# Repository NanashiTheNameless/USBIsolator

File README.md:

# USBIsolator

Simple USB isolator board project with two hardware variants:

- `USBIsolator.alt` is the smaller, simpler version and is the version currently used in production.
- `USBIsolator` is the full version and includes the switch-function cheatsheet in its README.

## Project folders:

- [USBIsolator](USBIsolator/) - full version (with cheatsheet)
- [USBIsolator.alt](USBIsolator.alt/) - compact production version

## Production files:

- [USBIsolator production](USBIsolator/production/)
- [USBIsolator.alt production](USBIsolator.alt/production/)

## Cheatsheet

- [USBIsolator.odt](USBIsolator.odt)

```text
SW1:
1 -> USB1: VCC =  USB2: VCC (DEFAULT: ON)
2 -> USB1: D-  =  USB2: D-  (DEFAULT: ON)
3 -> USB1: D+  =  USB2: D+  (DEFAULT: ON)
4 -> USB1: GND =  USB2: GND (DEFAULT: ON)
5 -> USB1: SH  =  USB2: SH  (DEFAULT: ON)

SW2:
1 -> USB2: SH  =  USB2: GND (DEFAULT: OFF)
2 -> USB1: SH  =  USB1: GND (DEFAULT: OFF)
```

## Images

### USBIsolator (full version)

### USBIsolator.alt (production version)

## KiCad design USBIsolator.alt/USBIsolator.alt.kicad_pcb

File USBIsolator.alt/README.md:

# USBIsolator

Simple USB isolator board project (compact production version).

This is the smaller and simpler variant currently used in production.

- For the full version, see [USBIsolator](../USBIsolator/).
- The same switch-function cheatsheet is included below.

## Project folders:

- [USBIsolator](../USBIsolator/) - full version (with cheatsheet)
- [USBIsolator.alt](./) - compact production version

## Production files:

- [USBIsolator production](../USBIsolator/production/)
- [USBIsolator.alt production](production/)

## Cheatsheet

- [USBIsolator.odt](../USBIsolator.odt)

```text
SW1:
1 -> USB1: VCC =  USB2: VCC (DEFAULT: ON)
2 -> USB1: D-  =  USB2: D-  (DEFAULT: ON)
3 -> USB1: D+  =  USB2: D+  (DEFAULT: ON)
4 -> USB1: GND =  USB2: GND (DEFAULT: ON)
5 -> USB1: SH  =  USB2: SH  (DEFAULT: ON)

SW2:
1 -> USB2: SH  =  USB2: GND (DEFAULT: OFF)
2 -> USB1: SH  =  USB1: GND (DEFAULT: OFF)
```

## Images

### USBIsolator.alt (production version)

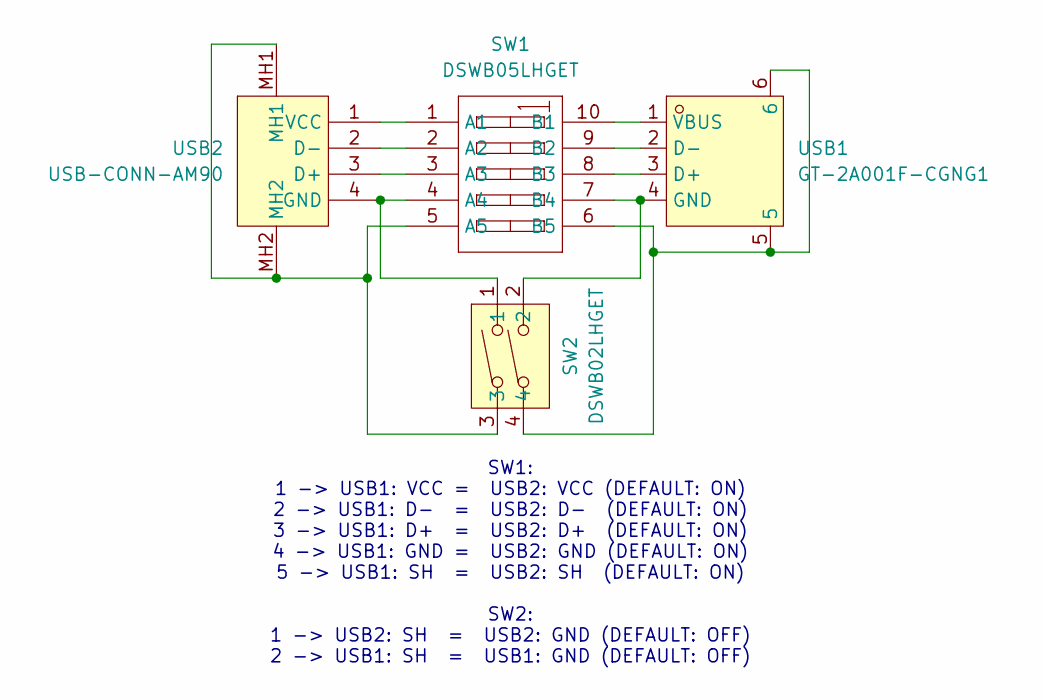
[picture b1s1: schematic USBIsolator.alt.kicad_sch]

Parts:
SW1: DSWB05LHGET; SW-TH_DSWB05LHGET; LCSC Part C126889
SW2: DSWB02LHGET; SW-TH_DSWB02LHGET; LCSC Part C99421
USB1: GT-2A001F-CGNG1; USB-A-TH_AF-90-ZJWG-ZB; LCSC Part C5362632
USB2: USB-CONN-AM90; USB-A-TH_AM90; LCSC Part C9739

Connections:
unnamed: SW1.1 (A1), USB2.1 (VCC)
unnamed: SW1.2 (A2), USB2.2 (D-)
unnamed: SW1.3 (A3), USB2.3 (D+)
unnamed: SW1.4 (A4), SW2.1, USB2.4 (GND)
unnamed: SW1.5 (A5), SW2.3, USB2.MH1, USB2.MH2
unnamed: SW1.10 (B1), USB1.1 (VBUS)
unnamed: SW1.9 (B2), USB1.2 (D-)
unnamed: SW1.8 (B3), USB1.3 (D+)
unnamed: SW1.7 (B4), SW2.2, USB1.4 (GND)
unnamed: SW1.6 (B5), SW2.4, USB1.5, USB1.6

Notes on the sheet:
SW1: 1 -> USB1: VCC = USB2: VCC (DEFAULT: ON) 2 -> USB1: D- = USB2: D- (DEFAULT: ON) 3 -> USB1: D+ = USB2: D+ (DEFAULT: ON) 4 -> USB1: GND = USB2: GND (DEFAULT: ON) 5 -> USB1: SH = USB2: SH (DEFAULT: ON) SW2: 1 -> USB2: SH = USB2: GND (DEFAULT: OFF) 2 -> USB1: SH = USB1: GND (DEFAULT: OFF)

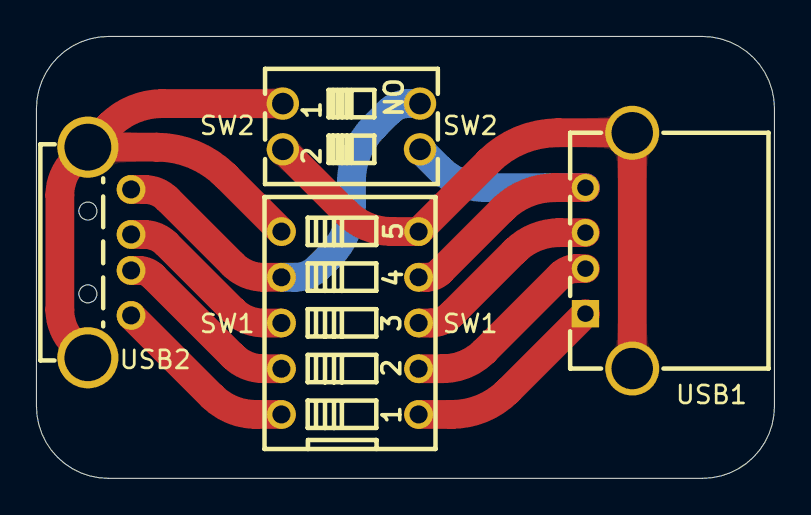
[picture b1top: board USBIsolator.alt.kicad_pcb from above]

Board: 2 copper layers, 41.0 x 24.5 mm, 4 parts (0 on the bottom side), 10 nets.

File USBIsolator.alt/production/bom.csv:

Designator,Footprint,Quantity,Value,LCSC Part #
SW1,SW-TH_DSWB05LHGET,1,DSWB05LHGET,C126889
SW2,SW-TH_DSWB02LHGET,1,DSWB02LHGET,C99421
USB1,USB-A-TH_AF-90-ZJWG-ZB,1,GT-2A001F-CGNG1,C5362632
USB2,USB-A-TH_AM90,1,USB-CONN-AM90,C9739

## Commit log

2025-01-11 Add license.md
2025-01-11 Add Initial (local) Version
2025-01-11 add image optimization workflows
2025-01-11 Compressed Images
2025-01-11 [ImgBot] Optimize images
    *Total -- 182.69kb -> 162.54kb (11.03%)
    /BoardF.png -- 103.21kb -> 87.80kb (14.93%)
    /BoardB.png -- 79.48kb -> 74.73kb (5.97%)
2025-01-11 Optimized images
2025-01-11 fix my dumb typo lol
2025-10-29 Update license from v1.2 to v1.3
    Updated the license from version 1.2 to 1.3, including changes to copyright links and obligations regarding the use of the work.
2026-04-17 chore: sync gitlab updates
2026-04-17 update workflow
2026-05-07 Update design files
